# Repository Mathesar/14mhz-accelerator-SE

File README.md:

# 14mhz-accelerator-SE
Special Edition of the 14MHz accelerator without local fastram and support for DMA masters

This version was especially created for owners of SCSI sidecars like the A590. 
It should support the DMA transfers of these sidecars.
This version also does away with the local 14MHz FAST RAM to reduce cost. 
Finally, this version uses the DIP version 68000 so one can retry overclocking the original CPU to make the design even cheaper.

IMPORTANT NOTE:
This design is UNTESTED AT THIS POINT. Use entirely at your own risk and have fun while doing so!

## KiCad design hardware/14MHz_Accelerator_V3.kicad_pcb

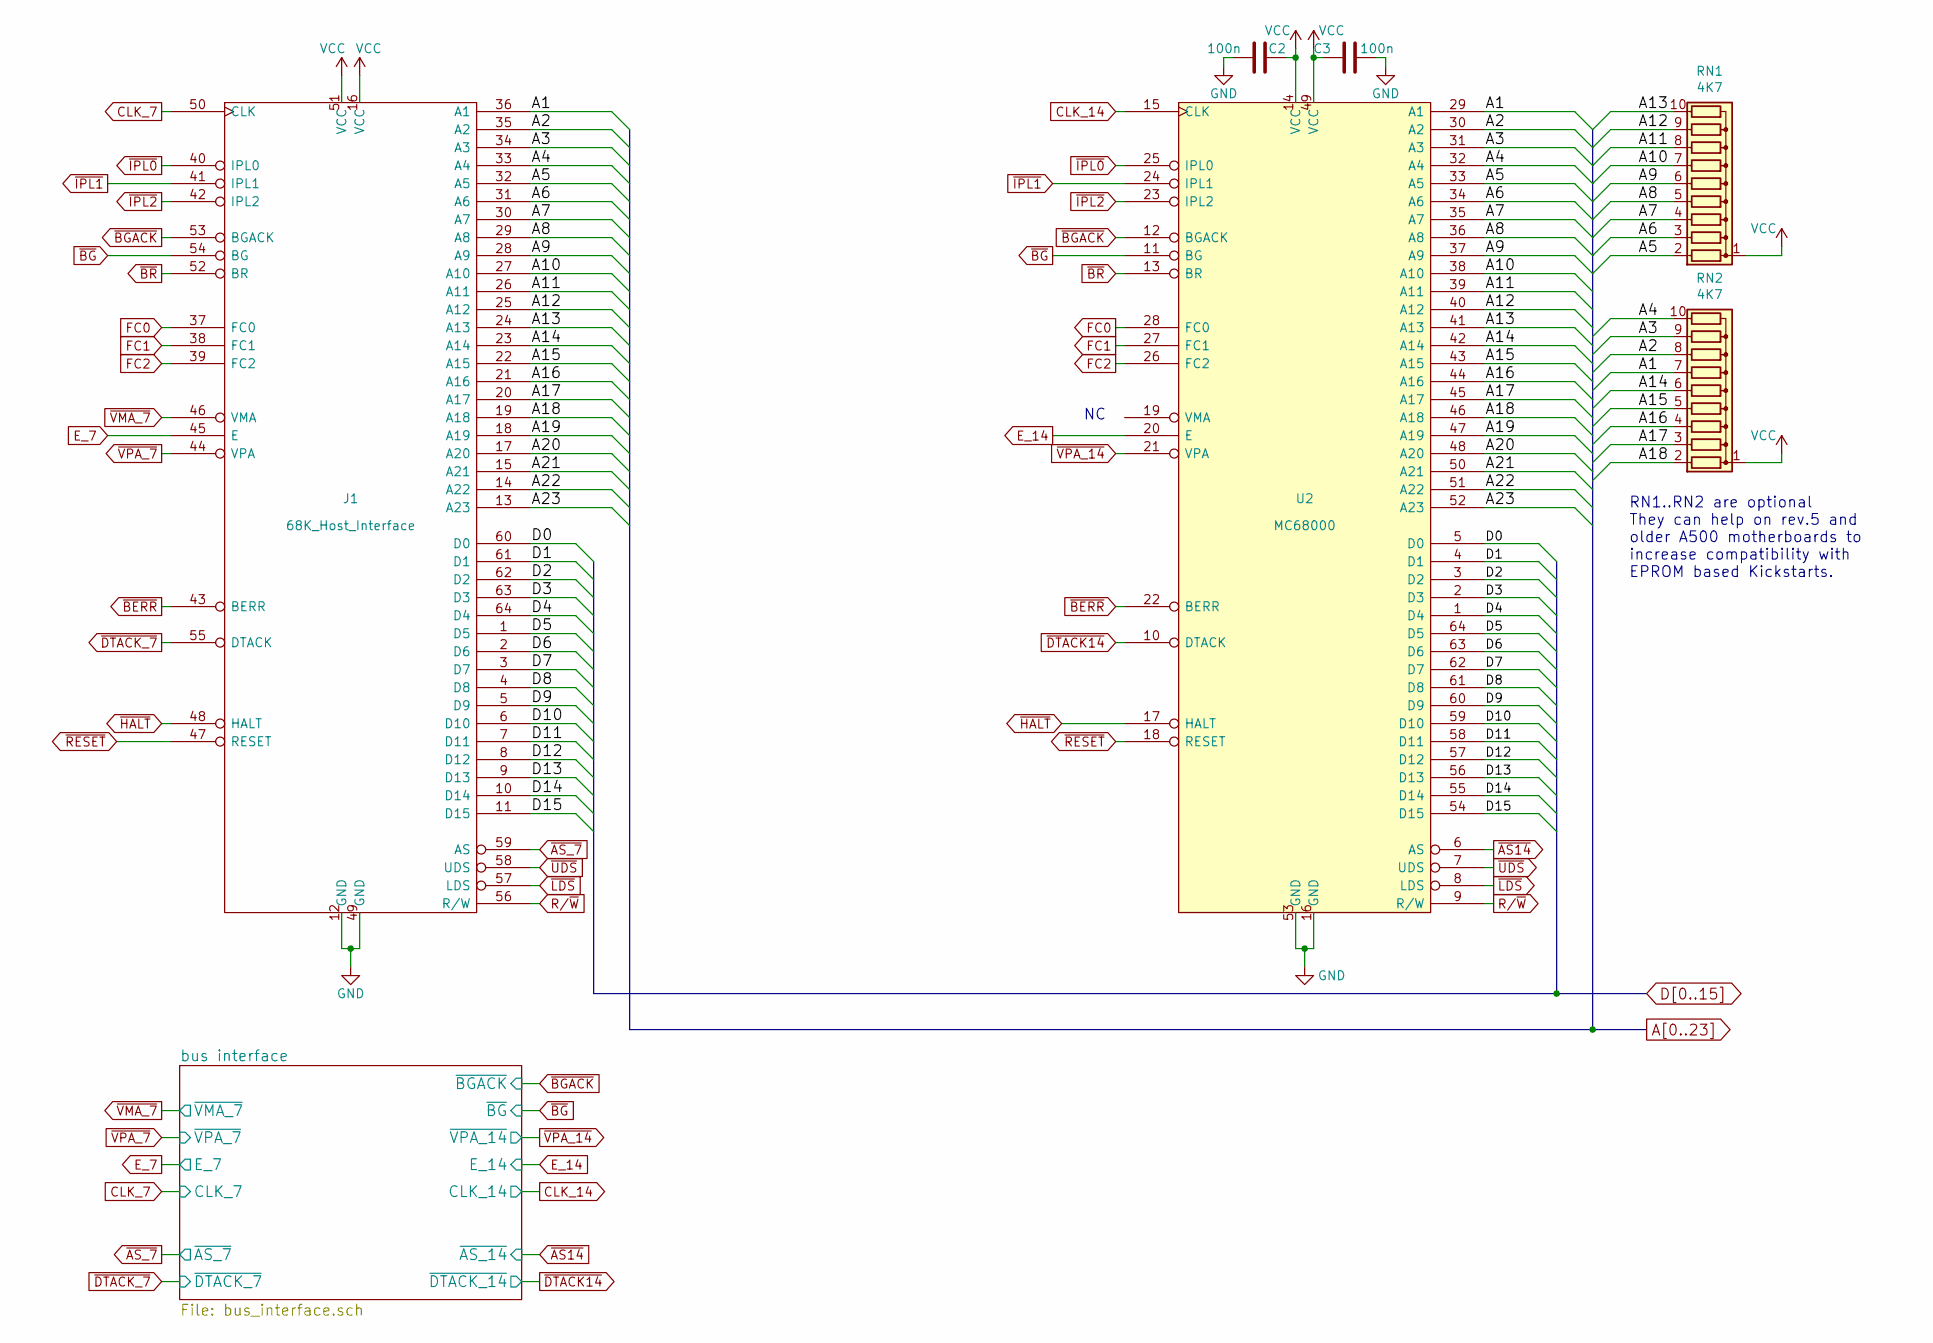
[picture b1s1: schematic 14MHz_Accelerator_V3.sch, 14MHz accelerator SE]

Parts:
C2, C3: 100n; C_0805_HandSoldering
J1: 68K_Host_Interface; DIP-64_W22.86mm
RN1, RN2: 4K7; R_Array_SIP10
U2: MC68000; DIP-64_W22.86mm

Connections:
A1: J1.36 (A1), RN2.7 (R6), U2.29 (A1)
A2: J1.35 (A2), RN2.8 (R7), U2.30 (A2)
A3: J1.34 (A3), RN2.9 (R8), U2.31 (A3)
A4: J1.33 (A4), RN2.10 (R9), U2.32 (A4)
A5: J1.32 (A5), RN1.2 (R1), U2.33 (A5)
A6: J1.31 (A6), RN1.3 (R2), U2.34 (A6)
A7: J1.30 (A7), RN1.4 (R3), U2.35 (A7)
A8: J1.29 (A8), RN1.5 (R4), U2.36 (A8)
A9: J1.28 (A9), RN1.6 (R5), U2.37 (A9)
A10: J1.27 (A10), RN1.7 (R6), U2.38 (A10)
A11: J1.26 (A11), RN1.8 (R7), U2.39 (A11)
A12: J1.25 (A12), RN1.9 (R8), U2.40 (A12)
A13: J1.24 (A13), RN1.10 (R9), U2.41 (A13)
A14: J1.23 (A14), RN2.6 (R5), U2.42 (A14)
A15: J1.22 (A15), RN2.5 (R4), U2.43 (A15)
A16: J1.21 (A16), RN2.4 (R3), U2.44 (A16)
A17: J1.20 (A17), RN2.3 (R2), U2.45 (A17)
A18: J1.19 (A18), RN2.2 (R1), U2.46 (A18)
A19: J1.18 (A19), U2.47 (A19)
A20: J1.17 (A20), U2.48 (A20)
A21: J1.15 (A21), U2.50 (A21)
A22: J1.14 (A22), U2.51 (A22)
A23: J1.13 (A23), U2.52 (A23)
CLK_7: J1.50 (CLK); also elsewhere on the board
CLK_14: U2.15 (CLK); also elsewhere on the board
D0: J1.60 (D0), U2.5 (D0)
D1: J1.61 (D1), U2.4 (D1)
D2: J1.62 (D2), U2.3 (D2)
D3: J1.63 (D3), U2.2 (D3)
D4: J1.64 (D4), U2.1 (D4)
D5: J1.1 (D5), U2.64 (D5)
D6: J1.2 (D6), U2.63 (D6)
D7: J1.3 (D7), U2.62 (D7)
D8: J1.4 (D8), U2.61 (D8)
D9: J1.5 (D9), U2.60 (D9)
D10: J1.6 (D10), U2.59 (D10)
D11: J1.7 (D11), U2.58 (D11)
D12: J1.8 (D12), U2.57 (D12)
D13: J1.9 (D13), U2.56 (D13)
D14: J1.10 (D14), U2.55 (D14)
D15: J1.11 (D15), U2.54 (D15)
E_7: J1.45 (E); also elsewhere on the board
E_14: U2.20 (E); also elsewhere on the board
FC0: J1.37 (FC0), U2.28 (FC0)
FC1: J1.38 (FC1), U2.27 (FC1)
FC2: J1.39 (FC2), U2.26 (FC2)
GND: C2.1, C3.2, J1.12 (GND), J1.49 (GND), U2.16 (GND), U2.53 (GND); also elsewhere on the board
R/~W: J1.56 (R/W), U2.9 (R/W)
VCC: C2.2, C3.1, J1.16 (VCC), J1.51 (VCC), RN1.1 (common), RN2.1 (common), U2.14 (VCC), U2.49 (VCC); also elsewhere on the board
~AS14: U2.6 (AS); also elsewhere on the board
~AS_7: J1.59 (AS); also elsewhere on the board
~BERR~: J1.43 (BERR), U2.22 (BERR)
~BGACK~: J1.53 (BGACK), U2.12 (BGACK); also elsewhere on the board
~BG~: J1.54 (BG), U2.11 (BG); also elsewhere on the board
~BR~: J1.52 (BR), U2.13 (BR)
~DTACK14: U2.10 (DTACK); also elsewhere on the board
~DTACK_7: J1.55 (DTACK); also elsewhere on the board
~HALT~: J1.48 (HALT), U2.17 (HALT)
~IPL0~: J1.40 (IPL0), U2.25 (IPL0)
~IPL1~: J1.41 (IPL1), U2.24 (IPL1)
~IPL2~: J1.42 (IPL2), U2.23 (IPL2)
~LDS: J1.57 (LDS), U2.8 (LDS)
~RESET~: J1.47 (RESET), U2.18 (RESET)
~UDS: J1.58 (UDS), U2.7 (UDS)
~VMA_7: J1.46 (VMA), U2.21 (VPA); also elsewhere on the board
~VPA_7: J1.44 (VPA); also elsewhere on the board

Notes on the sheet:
RN1..RN2 are optional They can help on rev.5 and older A500 motherboards to increase compatibility with EPROM based Kickstarts.

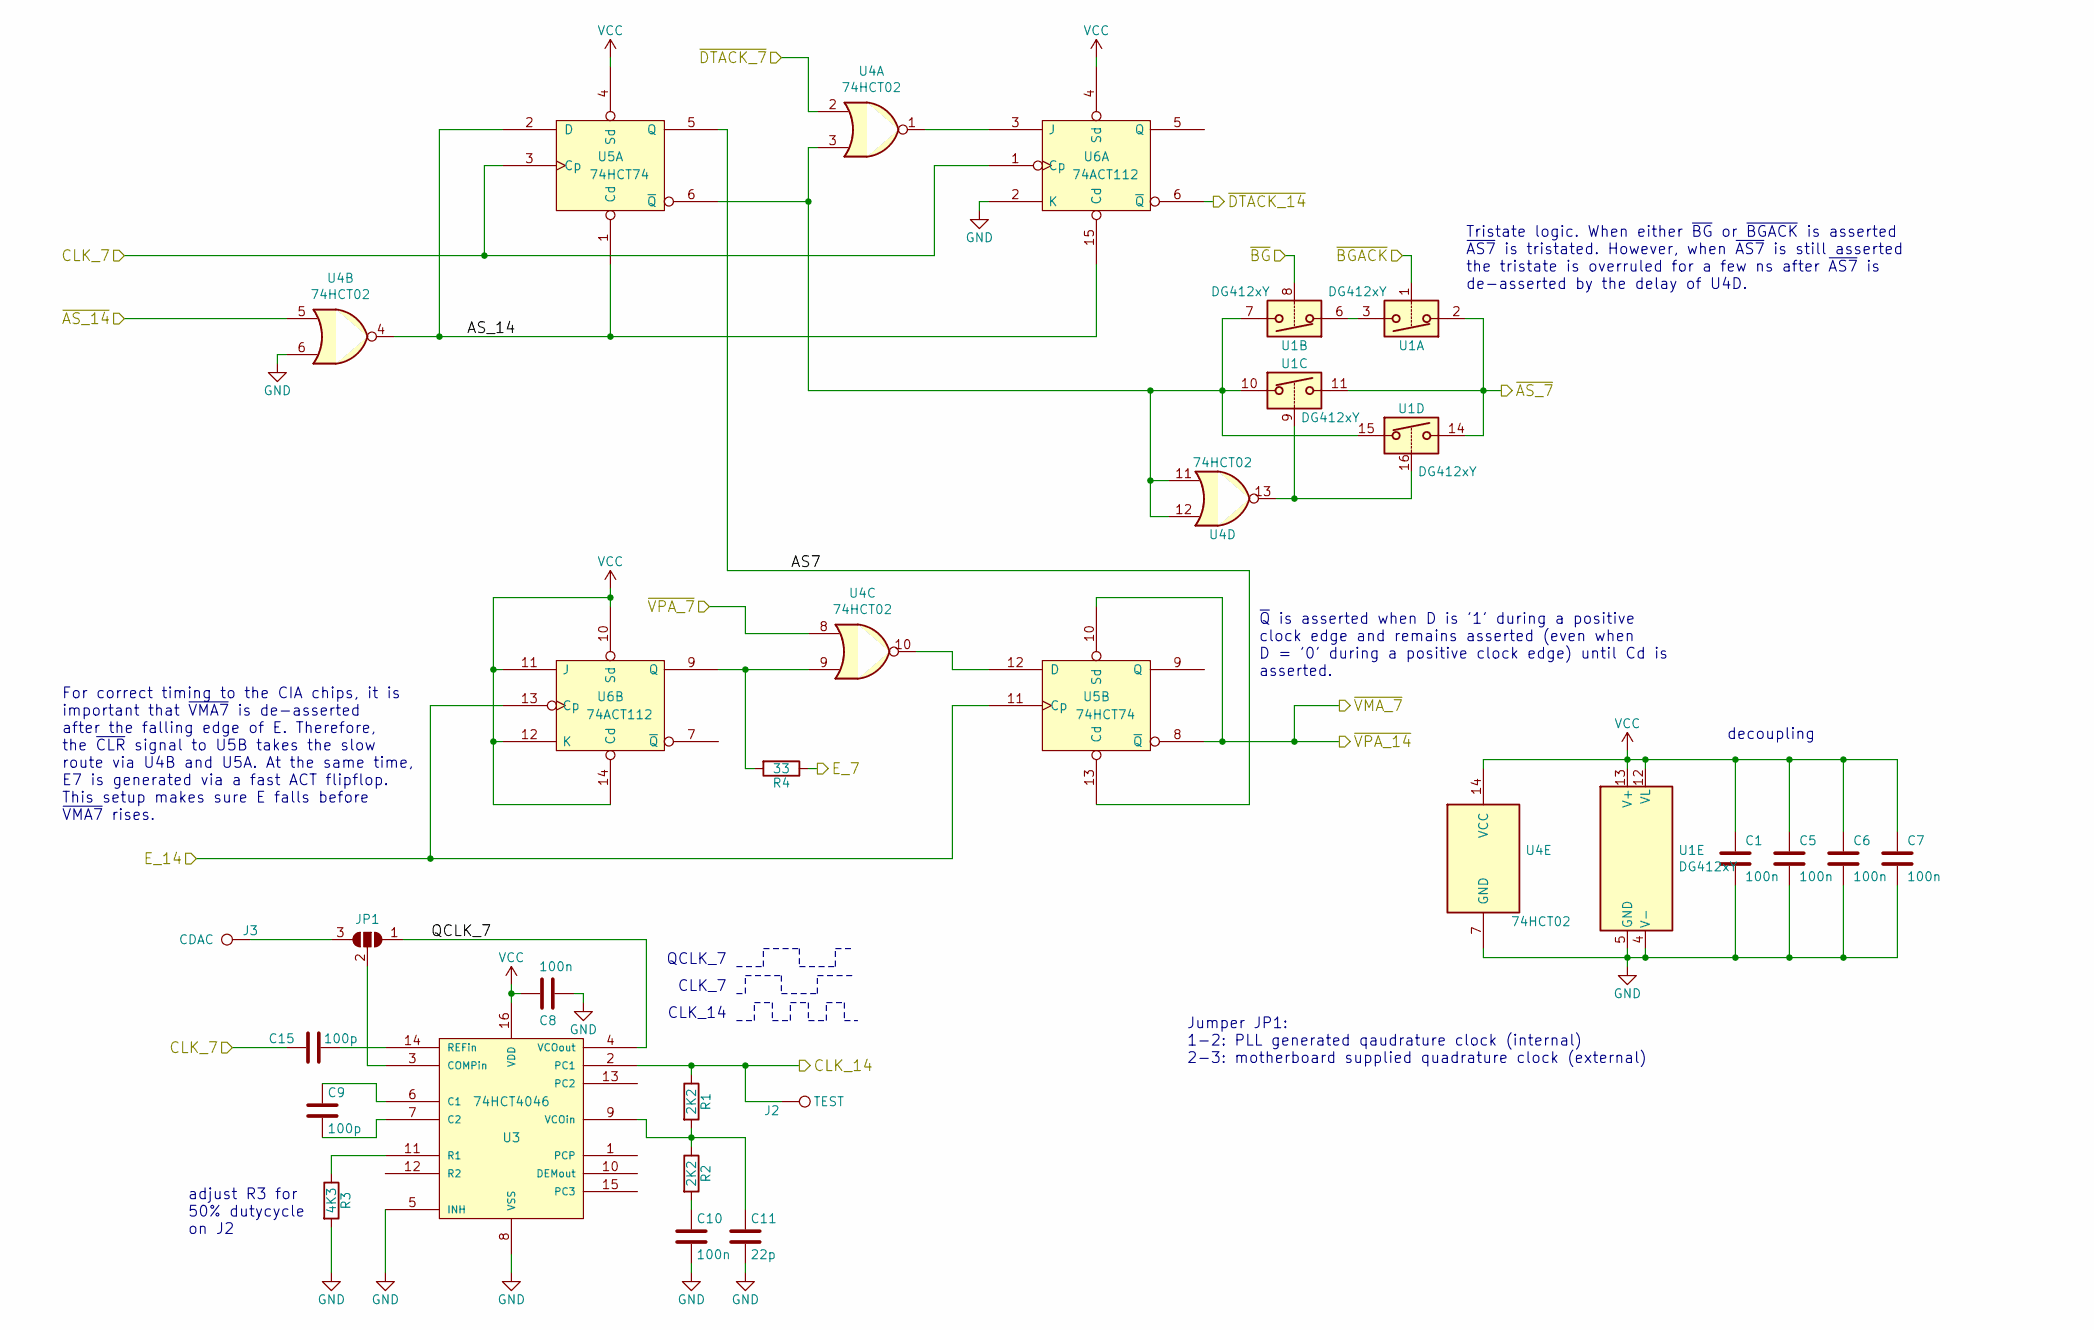
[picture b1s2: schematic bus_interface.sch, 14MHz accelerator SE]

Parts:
C1, C5, C6, C7, C8, C10: 100n; C_0805_HandSoldering
C9, C15: 100p; C_0805_HandSoldering
C11: 22p; C_0805_HandSoldering
J2: TEST; Pin_d1.0mm_L10.0mm
J3: CDAC; Pin_d1.0mm_L10.0mm
JP1: SolderJumper_3_Open; GS3
R1, R2: 2K2; R_0805_HandSoldering
R3: 4K3; R_0805_HandSoldering
R4: 33; R_0805_HandSoldering
U1: DG412xY; SOIC-16_3.9x9.9mm_P1.27mm
U3: 74HCT4046; SOIC-16_3.9x9.9mm_Pitch1.27mm
U4: 74HCT02; SOIC-14_3.9x8.7mm_Pitch1.27mm
U5: 74HCT74; SOIC-14_3.9x8.7mm_Pitch1.27mm
U6: 74ACT112; SOIC-16_3.9x9.9mm_Pitch1.27mm

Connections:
/bus interface/AS7: U5.5 (Q), U5.13 (Cd)
/bus interface/AS_14: U4.4, U5.1 (Cd), U5.2 (D), U6.15 (Cd)
/bus interface/QCLK_7: JP1.1 (A), U3.4 (VCOout)
CLK_7: C15.1, U5.3 (Cp), U6.1 (Cp); also elsewhere on the board
CLK_14: J2.1, R1.1, U3.2 (PC1); also elsewhere on the board
E_7: R4.1; also elsewhere on the board
E_14: U5.11 (Cp), U6.13 (Cp); also elsewhere on the board
GND: C1.2, C5.2, C6.2, C7.2, C8.1, C10.2, C11.2, R3.2, U1.4 (V-), U1.5 (GND), U3.5 (INH), U3.8 (VSS), U4.6, U4.7 (GND), U5.7 (GND), U6.2 (K), U6.8 (GND); also elsewhere on the board
unnamed: C9.1, U3.6 (C1)
unnamed: C9.2, U3.7 (C2)
unnamed: C10.1, R2.2
unnamed: C11.1, R1.2, R2.1, U3.9 (VCOin)
unnamed: C15.2, U3.14 (REFin)
unnamed: J3.1, JP1.3 (B)
unnamed: JP1.2 (C), U3.3 (COMPin)
unnamed: R3.1, U3.11 (R1)
unnamed: R4.2, U4.9, U6.9 (Q)
unnamed: U1.3, U1.6
unnamed: U1.7, U1.10, U1.15, U4.3, U4.11, U4.12, U5.6 (~Q)
unnamed: U1.9, U1.16, U4.13
unnamed: U4.1, U6.3 (J)
unnamed: U4.10, U5.12 (D)
VCC: C1.1, C5.1, C6.1, C7.1, C8.2, U1.12 (VL), U1.13 (V+), U3.16 (VDD), U4.14 (VCC), U5.4 (Sd), U5.14 (VCC), U6.4 (Sd), U6.10 (Sd), U6.11 (J), U6.12 (K), U6.14 (Cd), U6.16 (VCC); also elsewhere on the board
~AS14: U4.5; also elsewhere on the board
~AS_7: U1.2, U1.11, U1.14; also elsewhere on the board
~BGACK~: U1.1; also elsewhere on the board
~BG~: U1.8; also elsewhere on the board
~DTACK14: U6.6 (~Q); also elsewhere on the board
~DTACK_7: U4.2; also elsewhere on the board
~VMA_7: U5.8 (~Q), U5.10 (Sd); also elsewhere on the board
~VPA_7: U4.8; also elsewhere on the board

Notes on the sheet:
CLK_7
CLK_14
QCLK_7
adjust R3 for 50% dutycycle on J2
~Q~ is asserted when D is '1' during a positive clock edge and remains asserted (even when D = '0' during a positive clock edge) until Cd is asserted.
Jumper JP1: 1-2: PLL generated qaudrature clock (internal) 2-3: motherboard supplied quadrature clock (external)
For correct timing to the CIA chips, it is important that ~VMA7~ is de-asserted after the falling edge of E. Therefore, the ~CLR~ signal to U5B takes the slow route via U4B and U5A. At the same time, E7 is generated via a fast ACT flipflop. This setup makes sure E falls before ~VMA7~ rises.
Tristate logic. When either ~BG~ or ~BGACK~ is asserted ~AS7~ is tristated. However, when ~AS7~ is still asserted the tristate is overruled for a few ns after ~AS7~ is de-asserted by the delay of U4D.
decoupling

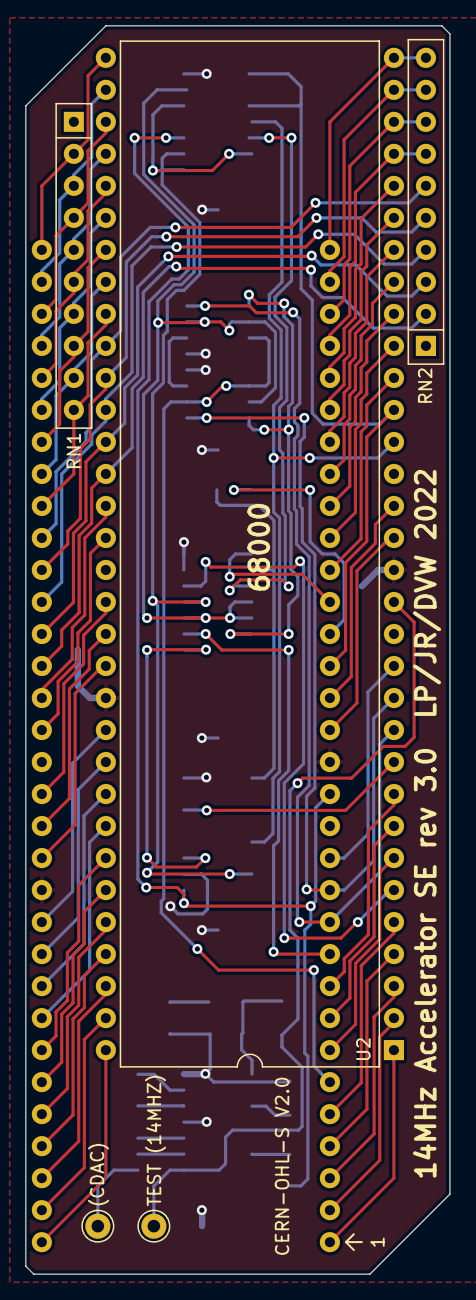
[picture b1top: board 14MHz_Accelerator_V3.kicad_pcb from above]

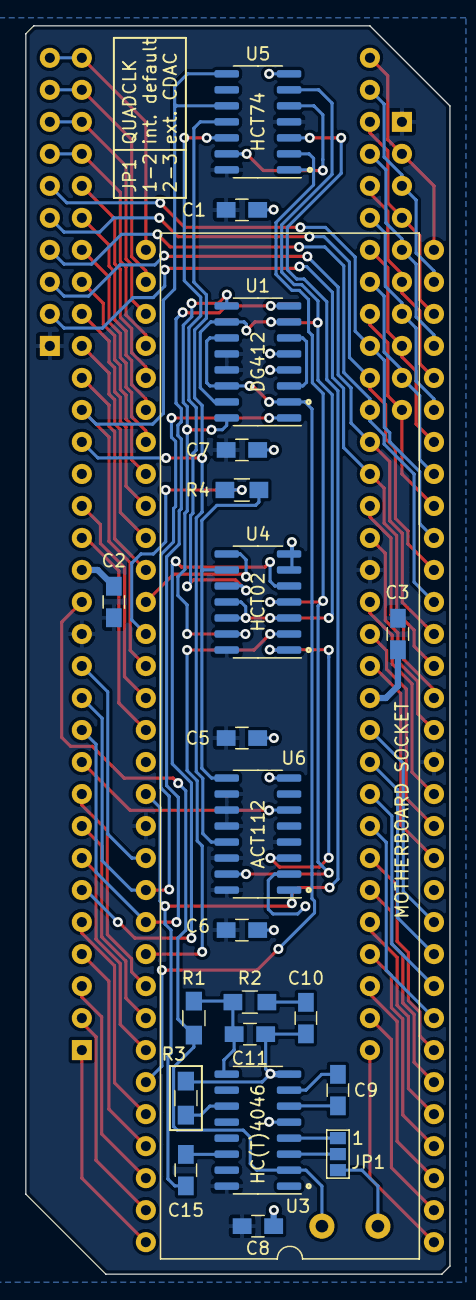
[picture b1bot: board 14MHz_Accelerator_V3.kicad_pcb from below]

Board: 2 copper layers, 33.7 x 99.1 mm, 27 parts (22 on the bottom side), 83 nets.

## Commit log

2022-08-17 first commit.
    UNTESTED DESIGN

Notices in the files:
hardware/14MHz_Accelerator_V3.kicad_pcb:
CERN-OHL-S V2.0
